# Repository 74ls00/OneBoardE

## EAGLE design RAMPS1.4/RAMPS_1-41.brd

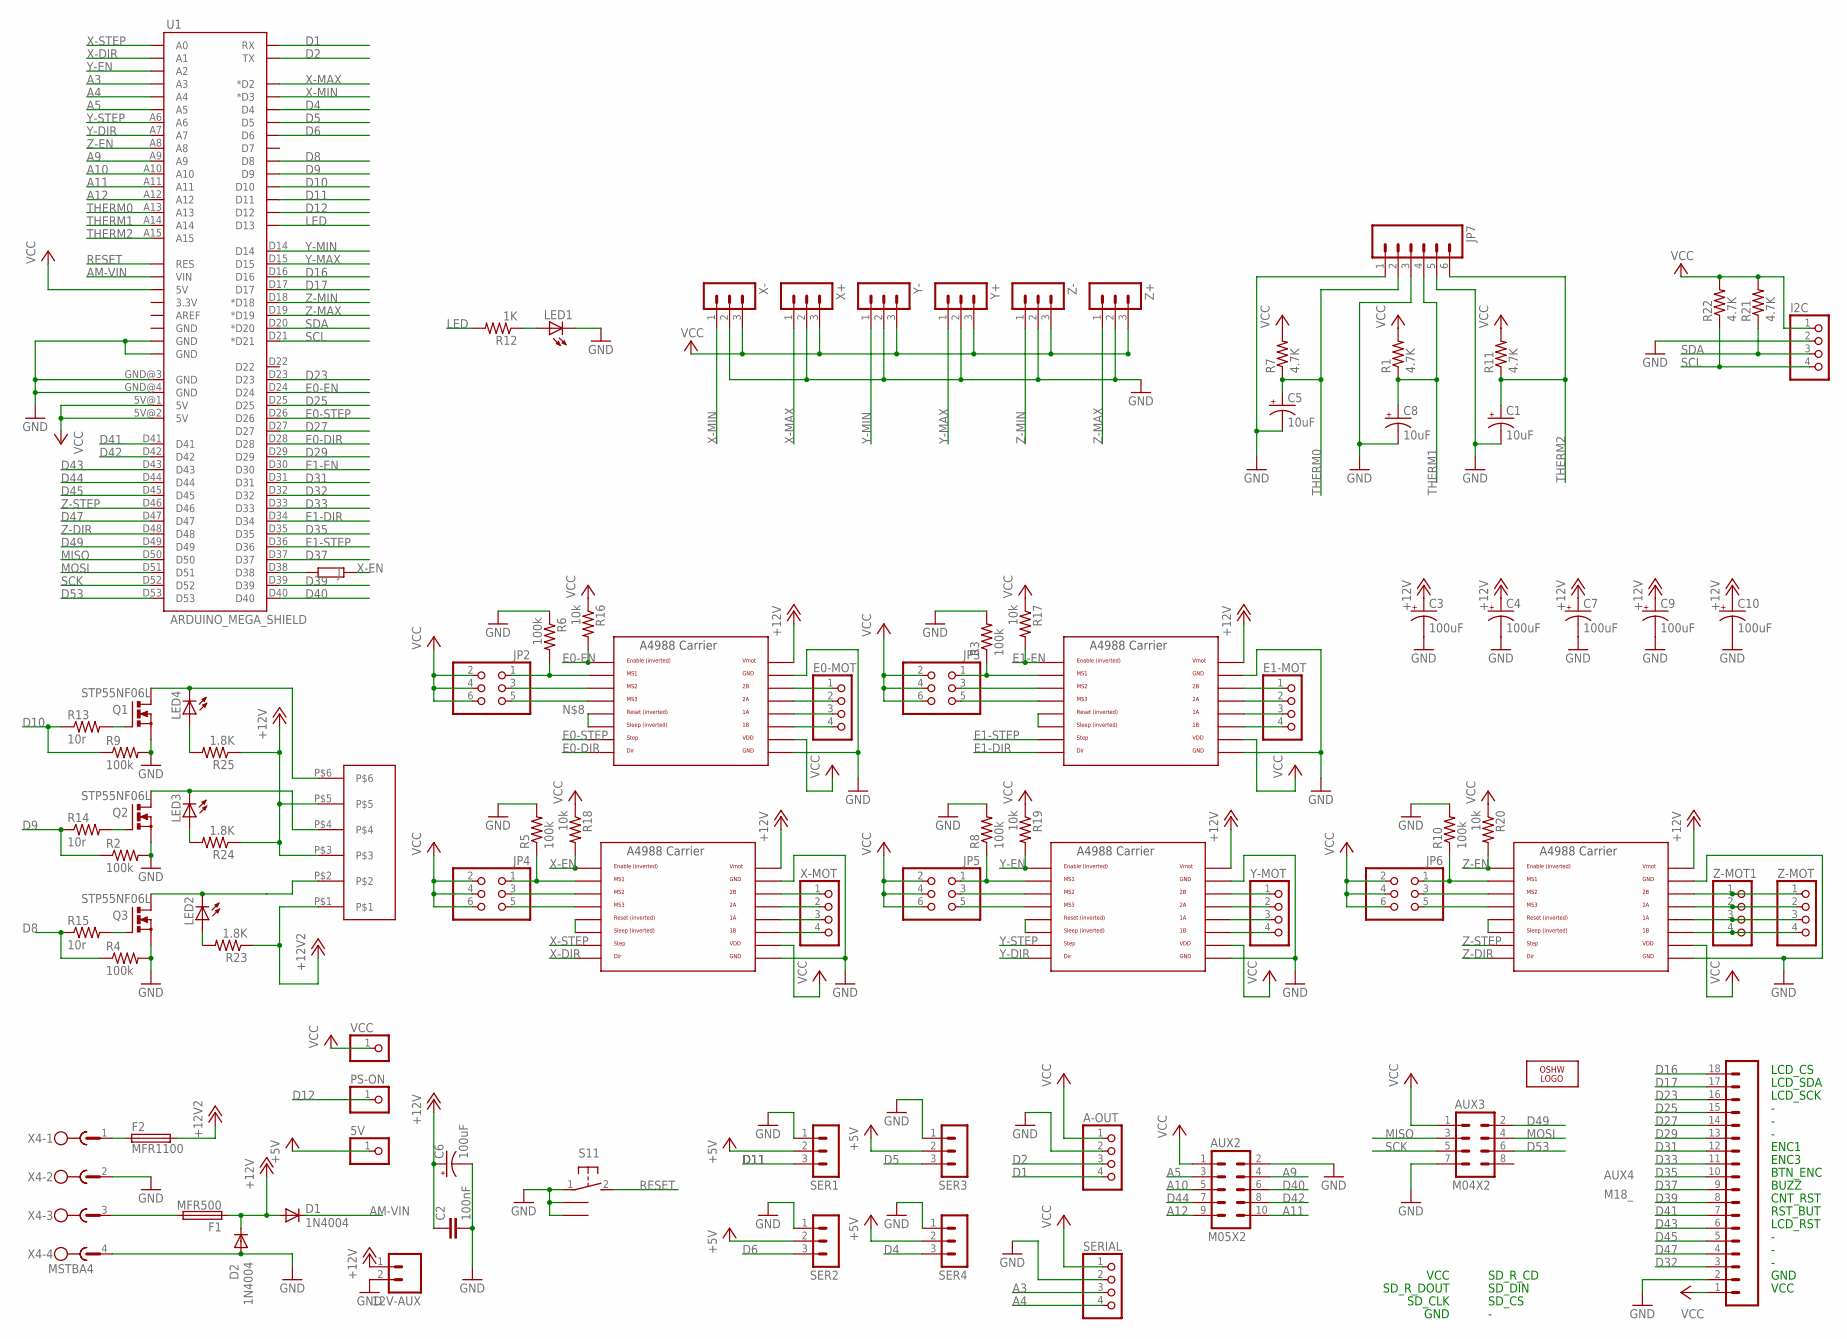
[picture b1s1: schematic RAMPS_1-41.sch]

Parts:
5V: PINHD-1X1; 1X01
12V-AUX: M02PTH; 1X02
A-OUT: PINHD-1X4; 1X04
AUX2: M05X2; 2X5
AUX3: M04X2; 2X4
AUX4: M18_; 1X18
C1, C5, C8: 10uF; 153CLV-0405
C2: 100nF; C0805
C3, C4, C6, C7, C9, C10: 100uF; 153CLV-0605
D1, D2: 1N4004; DO41-10
E0-MOT, E1-MOT: PINHD-1X4; 1X04
F1: MFR500
F2: MFR1100
I2C: PINHD-1X4; 1X04
J: R-EU_R1206W; R1206W
JP2, JP3, JP4, JP5, JP6: PINHD-2X3; 2X03
JP7: M06SIP; 1X06
LED1, LED2, LED3, LED4: LEDCHIP-LED0805; CHIP-LED0805
LOGO1: OSHW_LOGO_6MILX0100-NT; OSHW_6X100_NOTEXT
PS-ON: PINHD-1X1; 1X01
Q1, Q2, Q3: STP55NF06L; TO220BV
R1, R7, R11: 4.7K; R0805
R2, R3, R4, R5, R6, R8, R9: 100k; R0805
R10: 100k; R1206W
R12: 1K; R0805
R13, R15: 10r; R0805
R14: 10r; M0805
R16, R17, R18, R19, R20: 10k; R0805
R21, R22: 4.7K; R0603
R23, R24, R25: 1.8K; R0805
S1: 31-XX; B3F-31XX
SER1, SER2, SER3, SER4: 3PIN-HEADER
SERIAL: PINHD-1X4; 1X04
U1: ARDUINO_MEGA_SHIELD
U$2: 282837-6
U$4E0, U$5E1, U$6X, U$7Y: A4988BREAKOUT
VCC: PINHD-1X1; 1X01
X4: MSTBA4
X+: 3PIN-HEADER
X-: 3PIN-HEADER
X-MOT: PINHD-1X4; 1X04
Y+: 3PIN-HEADER
Y-: 3PIN-HEADER
Y-MOT: PINHD-1X4; 1X04
Z: A4988BREAKOUT
Z+: 3PIN-HEADER
Z-: 3PIN-HEADER
Z-MOT, Z-MOT1: PINHD-1X4; 1X04

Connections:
+5V: 5V.1, SER1.2, SER2.2, SER3.2, SER4.2
+12V: 12V-AUX.1, C2.1, C3.+, C4.+, C6.+, C7.+, C9.+, C10.+, D1.A, D2.C, F1.1, R24.1, R25.1, U$2.P$3, U$2.P$5, U$4E0.VMOT, U$5E1.VMOT, U$6X.VMOT, U$7Y.VMOT, Z.VMOT
+12V2: F2.2, R23.1, U$2.P$1
A3: SERIAL.3, U1.A3
A4: SERIAL.4, U1.A4
A5: AUX2.3, U1.A5
A9: AUX2.4, U1.A9
A10: AUX2.5, U1.A10
A11: AUX2.10, U1.A11
A12: AUX2.9, U1.A12
AM-VIN: D1.C, U1.VIN
D1: A-OUT.4, U1.RX
D2: A-OUT.3, U1.TX
D4: SER4.3, U1.D4
D5: SER3.3, U1.D5
D6: SER2.3, U1.D6
D8: R4.1, R15.1, U1.D8
D9: R2.1, R14.1, U1.D9
D10: R9.1, R13.1, U1.D10
D11: SER1.3, U1.D11
D12: PS-ON.1, U1.D12
D16: AUX4.18, U1.D16
D17: AUX4.17, U1.D17
D23: AUX4.16, U1.D23
D25: AUX4.15, U1.D25
D27: AUX4.14, U1.D27
D29: AUX4.13, U1.D29
D31: AUX4.12, U1.D31
D32: AUX4.3, U1.D32
D33: AUX4.11, U1.D33
D35: AUX4.10, U1.D35
D37: AUX4.9, U1.D37
D39: AUX4.8, U1.D39
D40: AUX2.6, U1.D40
D41: AUX4.7, U1.D41
D42: AUX2.8, U1.D42
D43: AUX4.6, U1.D43
D44: AUX2.7, U1.D44
D45: AUX4.5, U1.D45
D47: AUX4.4, U1.D47
D49: AUX3.2, U1.D49
D53: AUX3.6, U1.D53
E0-DIR: U1.D28, U$4E0.DIR
E0-EN: R16.2, U1.D24, U$4E0.EN
E0-STEP: U1.D26, U$4E0.STEP
E1-DIR: U1.D34, U$5E1.DIR
E1-EN: R17.2, U1.D30, U$5E1.EN
E1-STEP: U1.D36, U$5E1.STEP
GND: 12V-AUX.2, A-OUT.2, AUX2.2, AUX3.7, AUX4.2, C1.-, C2.2, C3.-, C4.-, C5.-, C6.-, C7.-, C8.-, C9.-, C10.-, D2.A, I2C.2, JP7.1, JP7.3, JP7.5, LED1.C, Q1.S, Q2.S, Q3.S, R2.2, R3.2, R4.2, R5.2, R6.1, R8.2, R9.2, R10.2, S1.1, S1.3, S1.4, SER1.1, SER2.1, SER3.1, SER4.1, SERIAL.2, U1.GND@0 (GND), U1.GND@1 (GND), U1.GND@3 (GND), U1.GND@4 (GND), U$4E0.GND, U$4E0.GND@0 (GND), U$5E1.GND, U$5E1.GND@0 (GND), U$6X.GND, U$6X.GND@0 (GND), U$7Y.GND, U$7Y.GND@0 (GND), X4.2, X4.4, X+.2, X-.2, Y+.2, Y-.2, Z.GND, Z.GND@0 (GND), Z+.2, Z-.2
LED: R12.2, U1.D13
MISO: AUX3.3, U1.D50
MOSI: AUX3.4, U1.D51
unnamed: LED3.C, Q2.D, U$2.P$4
unnamed: J.1, U1.D38
unnamed: E0-MOT.1, U$4E0.2B
unnamed: E0-MOT.2, U$4E0.2A
unnamed: JP2.1, R6.2, U$4E0.MS1
unnamed: JP2.5, U$4E0.MS3
unnamed: LED4.C, Q1.D, U$2.P$6
unnamed: U$4E0.RST, U$4E0.SLP (SLEEP)
unnamed: JP2.3, U$4E0.MS2
unnamed: E0-MOT.3, U$4E0.1A
unnamed: E0-MOT.4, U$4E0.1B
unnamed: E1-MOT.1, U$5E1.2B
unnamed: E1-MOT.2, U$5E1.2A
unnamed: JP4.1, R5.1, U$6X.MS1
unnamed: JP4.3, U$6X.MS2
unnamed: E1-MOT.3, U$5E1.1A
unnamed: JP5.3, U$7Y.MS2
unnamed: E1-MOT.4, U$5E1.1B
unnamed: JP4.5, U$6X.MS3
unnamed: U$6X.RST, U$6X.SLP (SLEEP)
unnamed: U$6X.2B, X-MOT.1
unnamed: U$6X.2A, X-MOT.2
unnamed: U$7Y.RST, U$7Y.SLP (SLEEP)
unnamed: U$5E1.RST, U$5E1.SLP (SLEEP)
unnamed: JP3.1, R3.1, U$5E1.MS1
unnamed: U$6X.1A, X-MOT.3
unnamed: U$6X.1B, X-MOT.4
unnamed: U$7Y.2B, Y-MOT.1
unnamed: U$7Y.2A, Y-MOT.2
unnamed: U$7Y.1A, Y-MOT.3
unnamed: JP5.5, U$7Y.MS3
unnamed: LED2.A, R23.2
unnamed: JP5.1, R8.1, U$7Y.MS1
unnamed: JP3.5, U$5E1.MS3
unnamed: JP3.3, U$5E1.MS2
unnamed: U$7Y.1B, Y-MOT.4
unnamed: JP6.3, Z.MS2
unnamed: Z.RST, Z.SLP (SLEEP)
unnamed: JP6.5, Z.MS3
unnamed: JP6.1, R10.1, Z.MS1
unnamed: Z.2B, Z-MOT.1, Z-MOT1.1
unnamed: Z.2A, Z-MOT.2, Z-MOT1.2
unnamed: Z.1A, Z-MOT.3, Z-MOT1.3
unnamed: Z.1B, Z-MOT.4, Z-MOT1.4
unnamed: LED3.A, R24.2
unnamed: LED1.A, R12.1
unnamed: Q2.G, R14.2
unnamed: Q1.G, R13.2
unnamed: Q3.G, R15.2
unnamed: LED4.A, R25.2
unnamed: LED2.C, Q3.D, U$2.P$2
unnamed: F2.1, X4.1
unnamed: F1.2, X4.3
RESET: S1.2 (S), U1.RES
SCK: AUX3.5, U1.D52
SCL: I2C.4, R22.1, U1.D21 (*D21)
SDA: I2C.3, R21.1, U1.D20 (*D20)
THERM0: C5.+, JP7.2, R7.1, U1.A13
THERM1: C8.+, JP7.4, R1.1, U1.A14
THERM2: C1.+, JP7.6, R11.1, U1.A15
VCC: A-OUT.1, AUX2.1, AUX3.1, AUX4.1, I2C.1, JP2.2, JP2.4, JP2.6, JP3.2, JP3.4, JP3.6, JP4.2, JP4.4, JP4.6, JP5.2, JP5.4, JP5.6, JP6.2, JP6.4, JP6.6, R1.2, R7.2, R11.2, R16.1, R17.1, R18.1, R19.1, R20.1, R21.2, R22.2, SERIAL.1, U1.5V@0 (5V), U1.5V@1 (5V), U1.5V@2 (5V), U$4E0.VDD, U$5E1.VDD, U$6X.VDD, U$7Y.VDD, VCC.1, X+.3, X-.3, Y+.3, Y-.3, Z.VDD, Z+.3, Z-.3
X-DIR: U1.A1, U$6X.DIR
X-EN: J.2, R18.2, U$6X.EN
X-MAX: U1.D2 (*D2), X+.1
X-MIN: U1.D3 (*D3), X-.1
X-STEP: U1.A0, U$6X.STEP
Y-DIR: U1.A7, U$7Y.DIR
Y-EN: R19.2, U1.A2, U$7Y.EN
Y-MAX: U1.D15, Y+.1
Y-MIN: U1.D14, Y-.1
Y-STEP: U1.A6, U$7Y.STEP
Z-DIR: U1.D48, Z.DIR
Z-EN: R20.2, U1.A8, Z.EN
Z-MAX: U1.D19 (*D19), Z+.1
Z-MIN: U1.D18 (*D18), Z-.1
Z-STEP: U1.D46, Z.STEP

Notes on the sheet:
VCC
GND
LCD_RST
RST_BUT
CNT_RST
BUZZ
BTN_ENC
ENC3
ENC1
LCD_SCK
LCD_SDA
LCD_CS
SD_CLK
SD_R_DOUT
SD_CS
SD_DIN
SD_R_CD

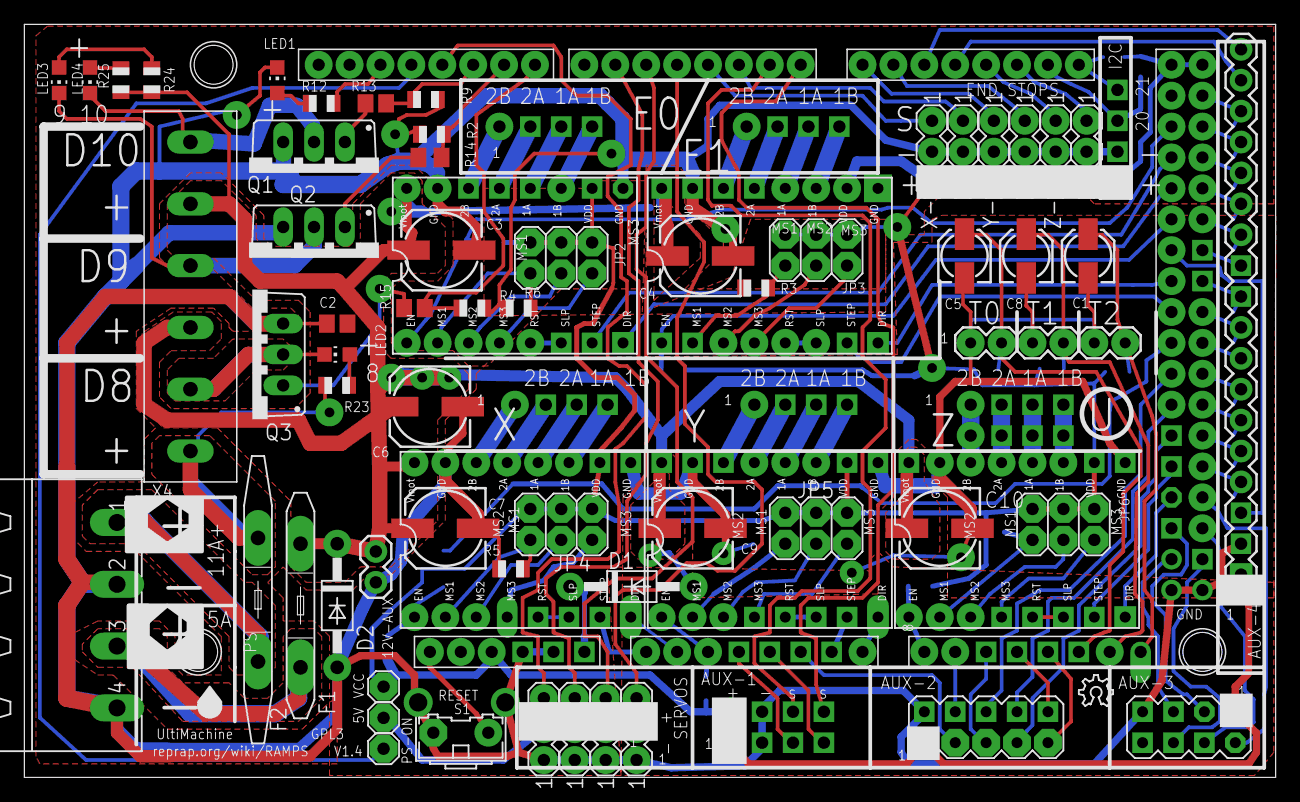
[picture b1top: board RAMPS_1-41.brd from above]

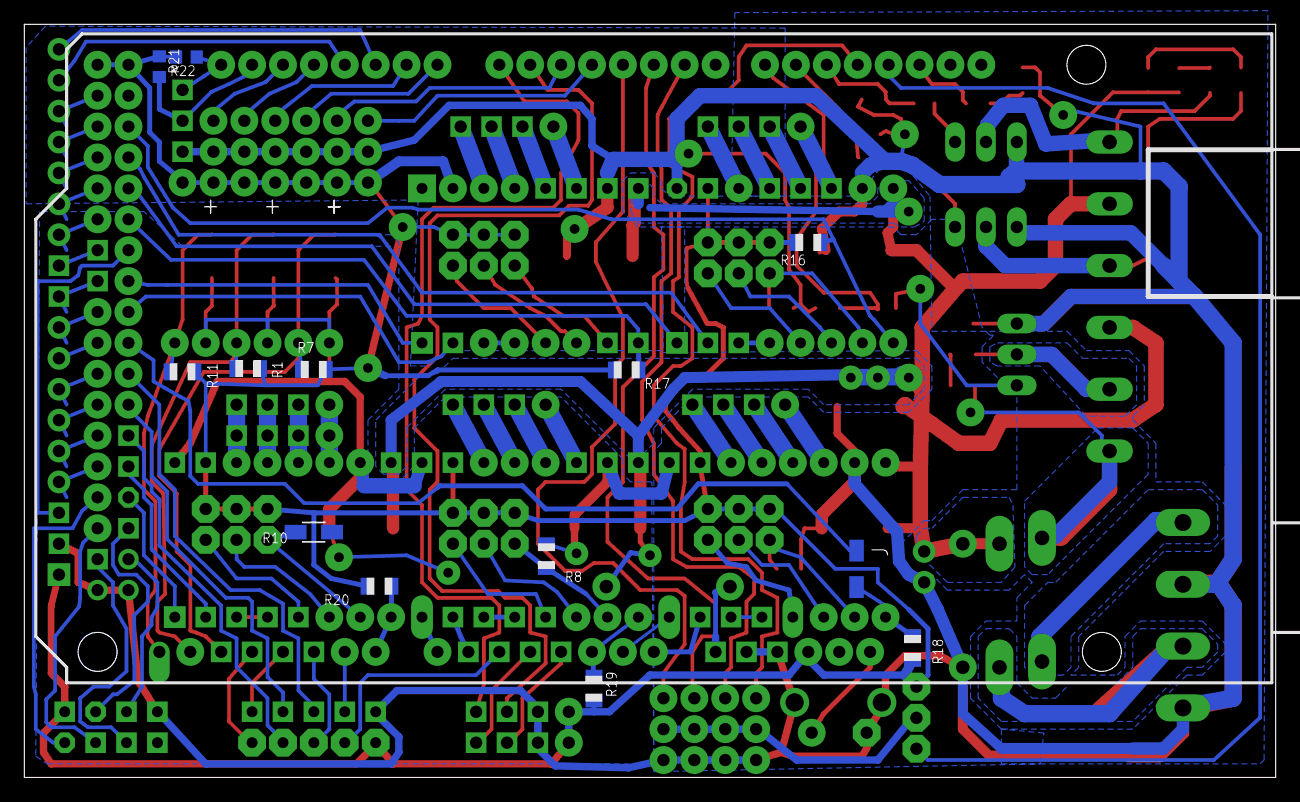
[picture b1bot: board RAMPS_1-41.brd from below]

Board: 2 copper layers, 102.9 x 61.9 mm, 89 parts (13 on the bottom side), 128 nets.

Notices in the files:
RAMPS1.4/RAMPS_1-41.brd:
GPL3
GPL v3
Copyright 2011 Johnny Russell - UltiMachine
